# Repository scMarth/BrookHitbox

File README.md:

# BrookHitbox
KiCad files for a Hitbox PCB meant to connect to a Brook board

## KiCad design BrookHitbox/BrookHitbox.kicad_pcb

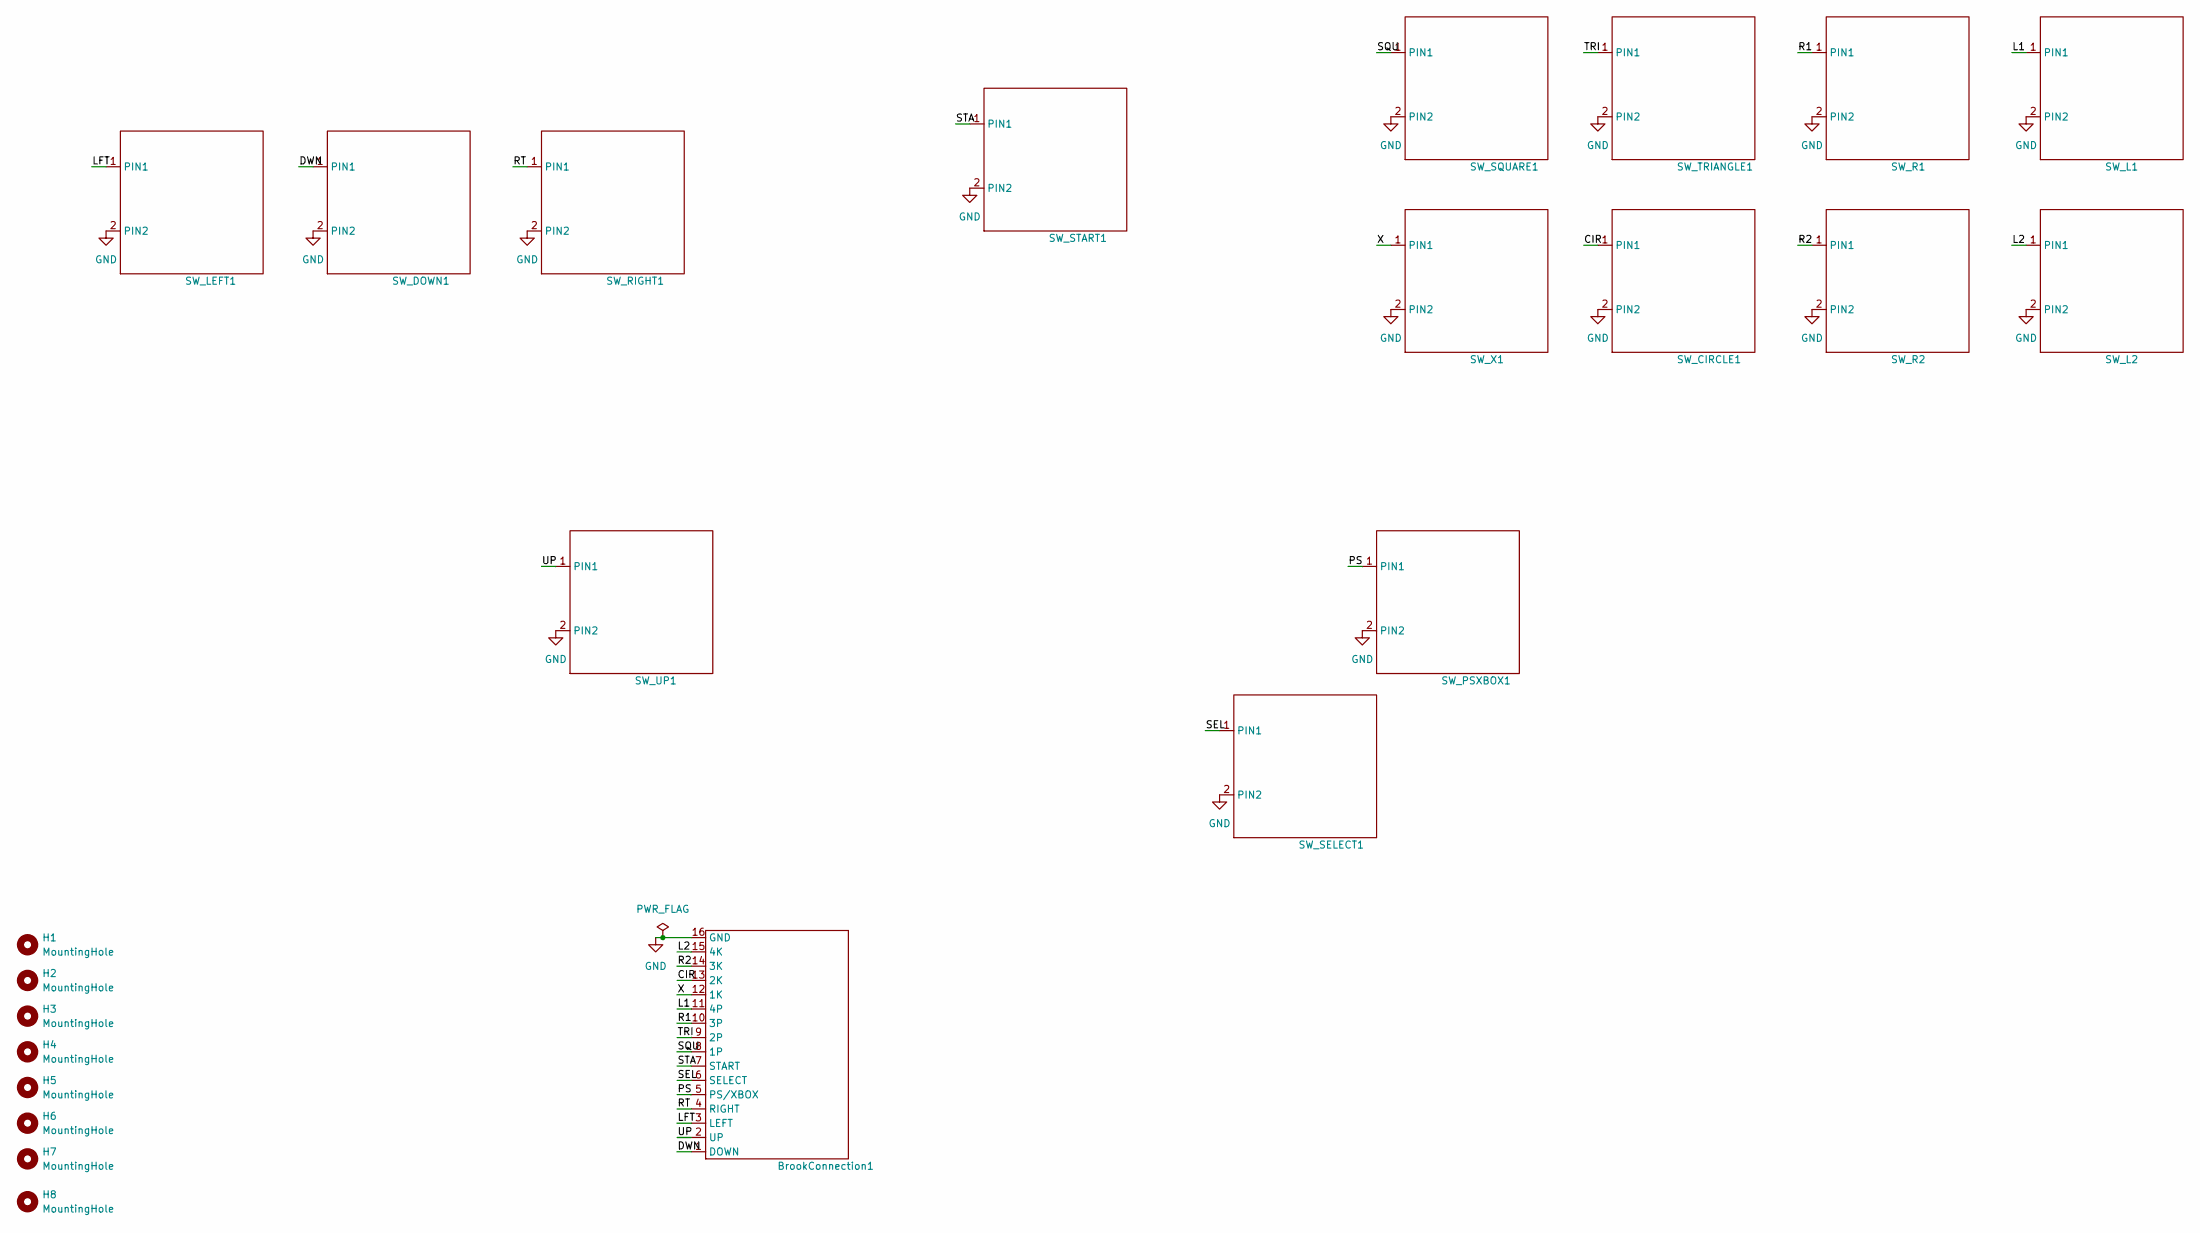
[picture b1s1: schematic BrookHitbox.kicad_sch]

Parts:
BrookConnection1: BrookConn16
H1, H2, H3, H4, H5, H6, H7, H8: MountingHole; MountingHole_2.2mm_M2
SW_CIRCLE1: SW_Cherry_MX_1.00u_PCB
SW_DOWN1: SW_Cherry_MX_1.00u_PCB
SW_L1, SW_L2: SW_Cherry_MX_1.00u_PCB
SW_LEFT1: SW_Cherry_MX_1.00u_PCB
SW_PSXBOX1: SW_Cherry_MX_1.00u_PCB
SW_R1, SW_R2: SW_Cherry_MX_1.00u_PCB
SW_RIGHT1: SW_Cherry_MX_1.00u_PCB
SW_SELECT1: SW_Cherry_MX_1.00u_PCB
SW_SQUARE1: SW_Cherry_MX_1.00u_PCB
SW_START1: SW_Cherry_MX_1.00u_PCB
SW_TRIANGLE1: SW_Cherry_MX_1.00u_PCB
SW_UP1: SW_Cherry_MX_1.00u_PCB
SW_X1: SW_Cherry_MX_1.00u_PCB

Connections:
/CIR: BrookConnection1.13 (2K), SW_CIRCLE1.1 (PIN1)
/DWN: BrookConnection1.1 (DOWN), SW_DOWN1.1 (PIN1)
/L1: BrookConnection1.11 (4P), SW_L1.1 (PIN1)
/L2: BrookConnection1.15 (4K), SW_L2.1 (PIN1)
/LFT: BrookConnection1.3 (LEFT), SW_LEFT1.1 (PIN1)
/PS: BrookConnection1.5 (PS/XBOX), SW_PSXBOX1.1 (PIN1)
/R1: BrookConnection1.10 (3P), SW_R1.1 (PIN1)
/R2: BrookConnection1.14 (3K), SW_R2.1 (PIN1)
/RT: BrookConnection1.4 (RIGHT), SW_RIGHT1.1 (PIN1)
/SEL: BrookConnection1.6 (SELECT), SW_SELECT1.1 (PIN1)
/SQU: BrookConnection1.8 (1P), SW_SQUARE1.1 (PIN1)
/STA: BrookConnection1.7 (START), SW_START1.1 (PIN1)
/TRI: BrookConnection1.9 (2P), SW_TRIANGLE1.1 (PIN1)
/UP: BrookConnection1.2 (UP), SW_UP1.1 (PIN1)
/X: BrookConnection1.12 (1K), SW_X1.1 (PIN1)
GND: BrookConnection1.16 (GND), SW_CIRCLE1.2 (PIN2), SW_DOWN1.2 (PIN2), SW_L1.2 (PIN2), SW_L2.2 (PIN2), SW_LEFT1.2 (PIN2), SW_PSXBOX1.2 (PIN2), SW_R1.2 (PIN2), SW_R2.2 (PIN2), SW_RIGHT1.2 (PIN2), SW_SELECT1.2 (PIN2), SW_SQUARE1.2 (PIN2), SW_START1.2 (PIN2), SW_TRIANGLE1.2 (PIN2), SW_UP1.2 (PIN2), SW_X1.2 (PIN2)

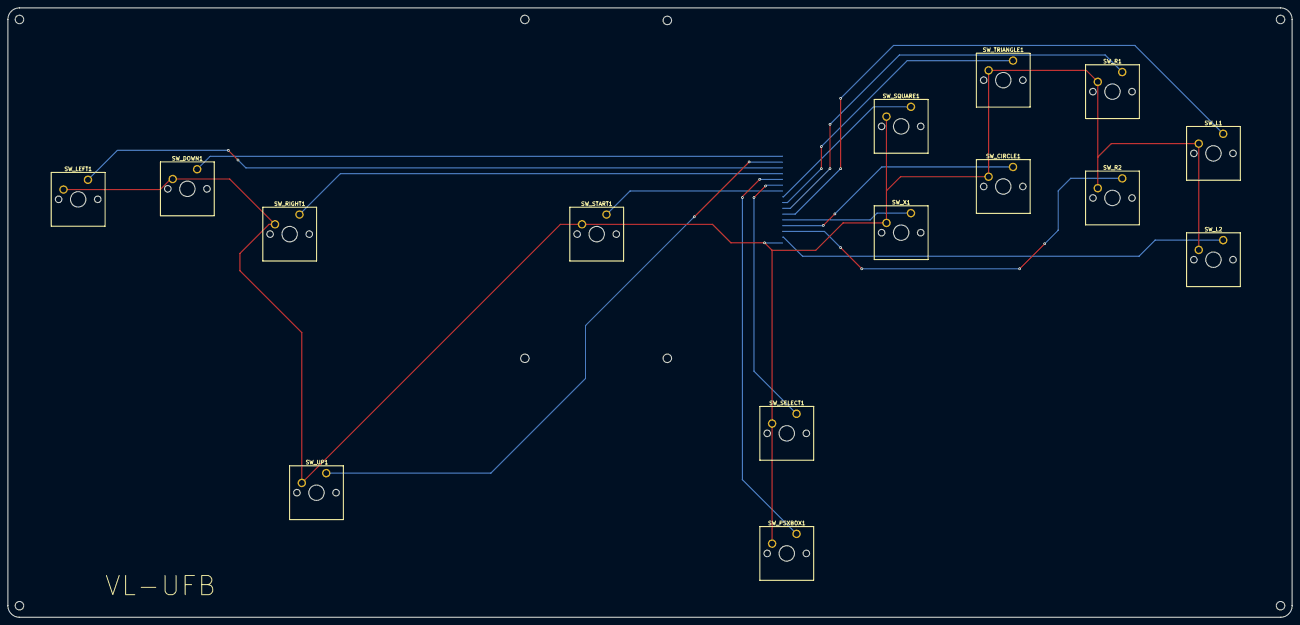
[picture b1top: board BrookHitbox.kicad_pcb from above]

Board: 2 copper layers, 333.5 x 158.2 mm, 24 parts (1 on the bottom side), 16 nets.

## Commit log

2023-07-08 schematic skeleton
2023-07-09 notes
2023-07-11 scrapwork script for calculating coordinates
2023-07-11 fix ERC errors, fix ratsnest not showing
2023-07-11 update pcb layout
2023-07-16 pcb layout placement for buttons
2023-07-25 add mounting holes
2023-07-28 mounting hole placement
2023-07-28 edge cuts
2023-07-28 traces
2023-07-29 generated gerber
2023-08-06 update notes
2023-08-06 add folder for rev 1
